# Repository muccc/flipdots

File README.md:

**Moved to https://git.muc.ccc.de/muccc/flipdots**

Software for some flipdot pannels we have.

http://wiki.muc.ccc.de/flipdot:start

ethersex-flipdot is a submodule which contains
firmware to receive and display data via ethernet.

netfbd is a submodule which contains a daemon
to grab parts of a linux framebuffer and send
via ethernet to the flipdots.

To init these submodules run 'git submodule init'
and 'git submodule update'.

When updating the repository, make sure to also run
'git submodule init' again, to get the lastest
changes inside the submodules.

scripts/ contains support scripts to send raw
test data to the flipdots.

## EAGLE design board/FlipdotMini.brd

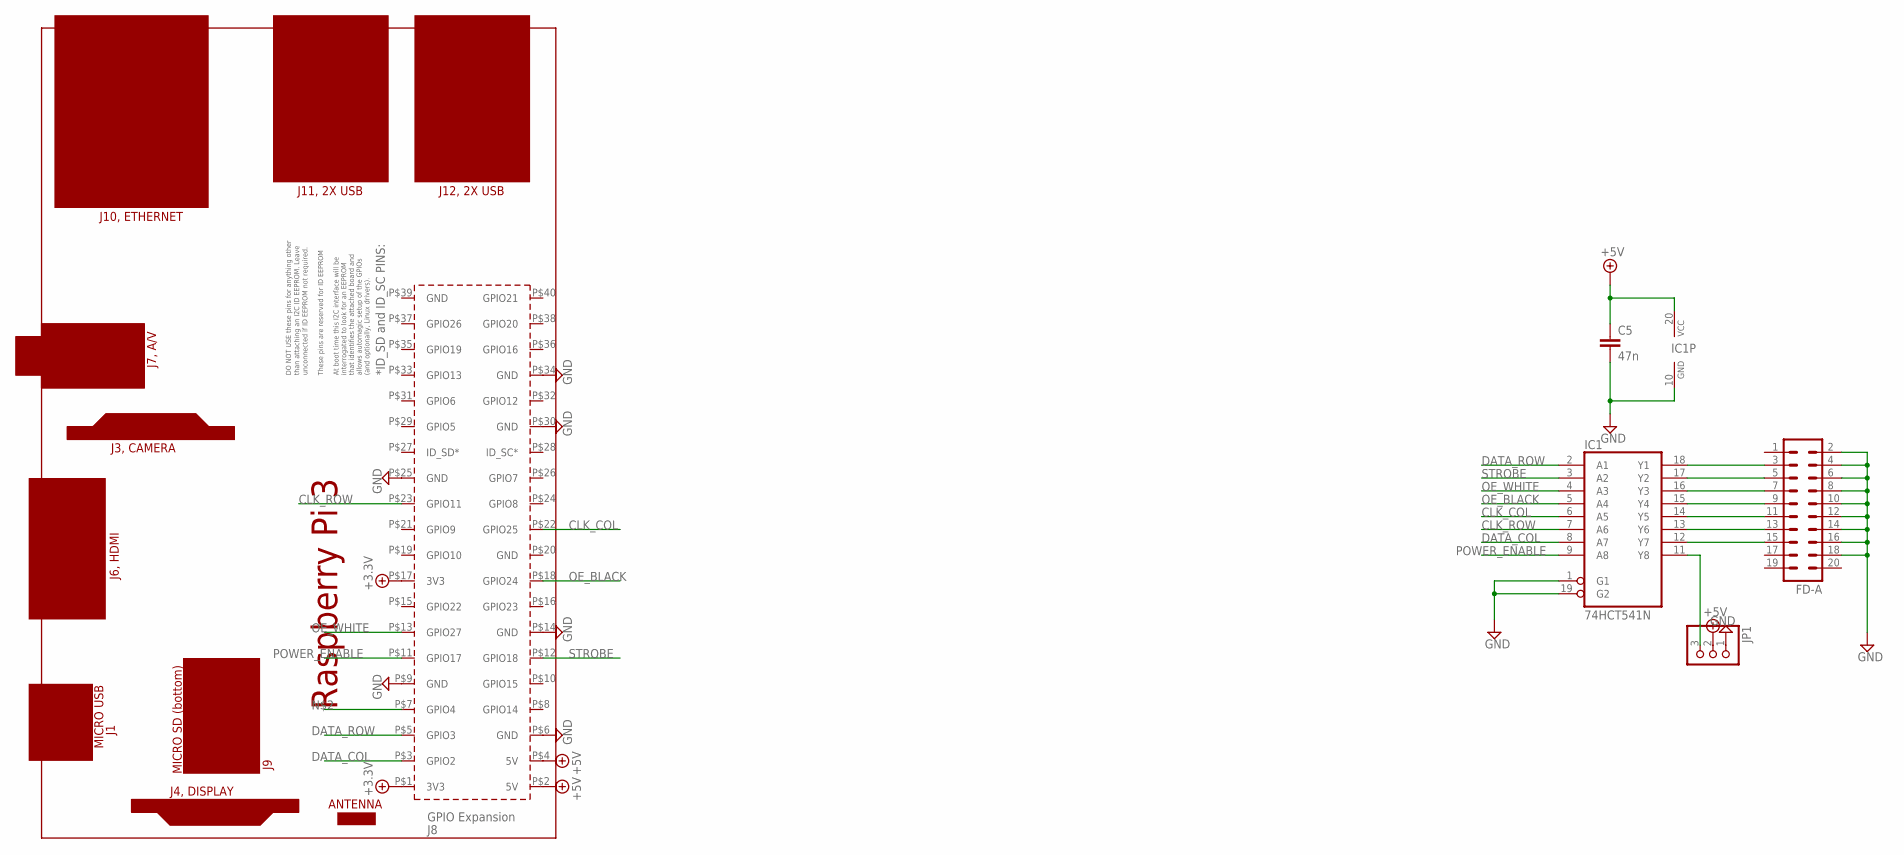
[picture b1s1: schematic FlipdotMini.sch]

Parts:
C5: 47n; C0805
FD-A: MA10-2
IC1: 74HCT541N; DIL20
JP1: PINHD-1X3; 1X03
PCB1: RPI3

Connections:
+3.3V: PCB1.P$1 (3V3), PCB1.P$17 (3V3)
+5V: C5.1, IC1.20 (VCC), JP1.2, PCB1.P$2 (5V), PCB1.P$4 (5V)
CLK_COL: IC1.6 (A5), PCB1.P$22 (GPIO25)
CLK_ROW: IC1.7 (A6), PCB1.P$23 (GPIO11)
DATA_COL: IC1.8 (A7), PCB1.P$3 (GPIO2)
DATA_ROW: IC1.2 (A1), PCB1.P$5 (GPIO3)
GND: C5.2, FD-A.2, FD-A.4, FD-A.6, FD-A.8, FD-A.10, FD-A.12, FD-A.14, FD-A.16, FD-A.18, IC1.1 (G1), IC1.10 (GND), IC1.19 (G2), JP1.1, PCB1.P$6 (GND), PCB1.P$9 (GND), PCB1.P$14 (GND), PCB1.P$25 (GND), PCB1.P$30 (GND), PCB1.P$34 (GND)
unnamed: FD-A.3, IC1.18 (Y1)
unnamed: FD-A.5, IC1.17 (Y2)
unnamed: FD-A.7, IC1.16 (Y3)
unnamed: FD-A.9, IC1.15 (Y4)
unnamed: FD-A.11, IC1.14 (Y5)
unnamed: FD-A.13, IC1.13 (Y6)
unnamed: FD-A.15, IC1.12 (Y7)
unnamed: IC1.11 (Y8), JP1.3
OE_BLACK: IC1.5 (A4), PCB1.P$18 (GPIO24)
OE_WHITE: IC1.4 (A3), PCB1.P$13 (GPIO27)
POWER_ENABLE: IC1.9 (A8), PCB1.P$11 (GPIO17)
STROBE: IC1.3 (A2), PCB1.P$12 (GPIO18)

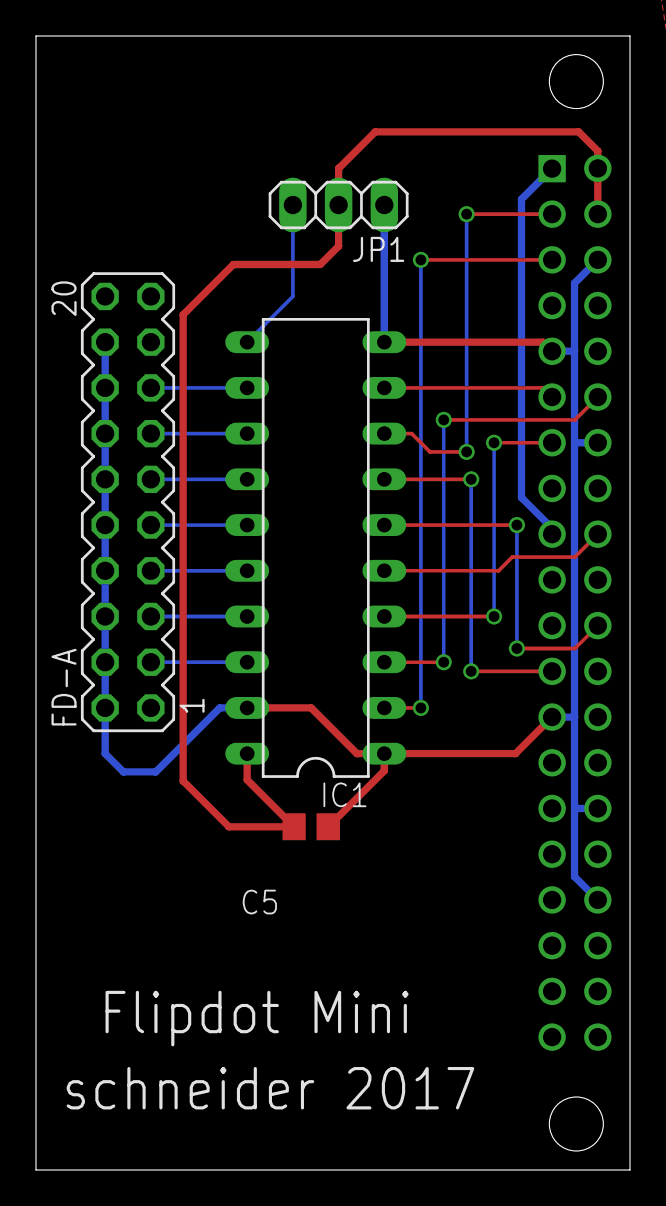
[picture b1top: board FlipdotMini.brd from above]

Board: 2 copper layers, 33.0 x 63.0 mm, 5 parts (0 on the bottom side), 19 nets.

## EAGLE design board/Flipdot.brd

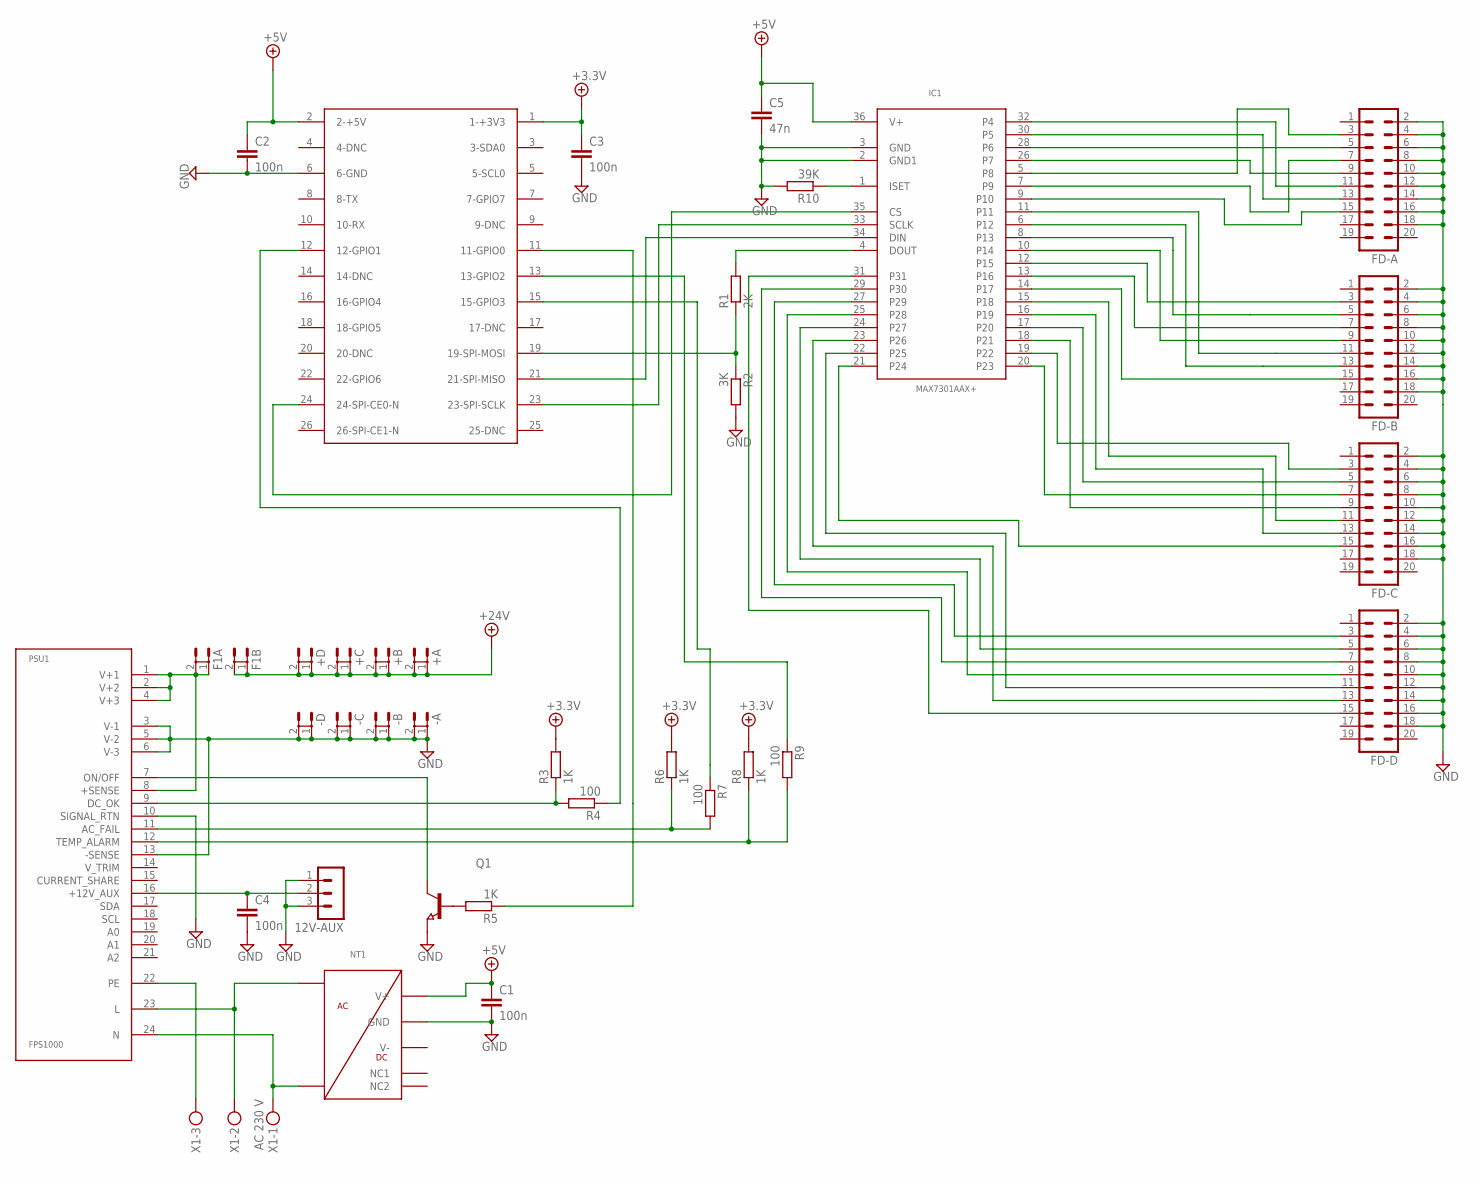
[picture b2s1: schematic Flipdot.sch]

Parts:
12V-AUX: MA03-1
+A: ST6,3
+B: ST6,3
+C: ST6,3
+D: ST6,3
-A: ST6,3
-B: ST6,3
-C: ST6,3
-D: ST6,3
C1, C2, C3, C4: 100n; C0603
C5: 47n; C0603
F1A, F1B: ST6,3
FD-A: MA10-2
FD-B: MA10-2
FD-C: MA10-2
FD-D: MA10-2
IC1: MAX7301AAX+; SSOP36
NT1: TMPM04; TPM04
PSU1: FPS1000; 24W9F
Q1: NPN-TRANSISTOR_SOT23; SOT23
R1: 2K; R0603
R2: 3K; R0603
R3, R5, R6, R8: 1K; R0603
R4, R7, R9: 100; R0603
R10: 39K; R0603
U$1: RASPBERRY-PI
X1: AC 230 V; MKDSN1,5/3-5,08

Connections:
+3.3V: C3.1, R3.2, R6.2, R8.2, U$1.1 (1-+3V3)
+5V: C1.1, C2.1, C5.1, IC1.36 (V+), NT1.3 (V+), U$1.2 (2-+5V)
+24V: +A.1, +A.2, +B.1, +B.2, +C.1, +C.2, +D.1, +D.2, F1B.1, F1B.2
GND: 12V-AUX.1, 12V-AUX.3, -A.1, -A.2, -B.1, -B.2, -C.1, -C.2, -D.1, -D.2, C1.2, C2.2, C3.2, C4.2, C5.2, FD-A.2, FD-A.4, FD-A.6, FD-A.8, FD-A.10, FD-A.12, FD-A.14, FD-A.16, FD-A.18, FD-B.2, FD-B.4, FD-B.6, FD-B.8, FD-B.10, FD-B.12, FD-B.14, FD-B.16, FD-B.18, FD-C.2, FD-C.4, FD-C.6, FD-C.8, FD-C.10, FD-C.12, FD-C.14, FD-C.16, FD-C.18, FD-D.2, FD-D.4, FD-D.6, FD-D.8, FD-D.10, FD-D.12, FD-D.14, FD-D.16, FD-D.18, IC1.2 (GND1), IC1.3 (GND), NT1.4 (GND), PSU1.3 (V-1), PSU1.5 (V-2), PSU1.6 (V-3), PSU1.10 (SIGNAL_RTN), PSU1.13 (-SENSE), Q1.2 (E), R2.2, R10.2, U$1.6 (6-GND)
unnamed: FD-D.11, IC1.22 (P25)
unnamed: FD-D.13, IC1.23 (P26)
unnamed: FD-A.5, IC1.28 (P6)
unnamed: FD-A.9, IC1.26 (P7)
unnamed: FD-A.3, IC1.5 (P8)
unnamed: FD-A.7, IC1.7 (P9)
unnamed: FD-A.15, IC1.9 (P10)
unnamed: FD-B.5, IC1.8 (P13)
unnamed: FD-B.9, IC1.10 (P14)
unnamed: FD-B.3, IC1.12 (P15)
unnamed: FD-B.7, IC1.13 (P16)
unnamed: FD-B.15, IC1.14 (P17)
unnamed: FD-C.5, IC1.17 (P20)
unnamed: FD-C.9, IC1.18 (P21)
unnamed: FD-C.3, IC1.19 (P22)
unnamed: FD-C.7, IC1.20 (P23)
unnamed: FD-C.15, IC1.21 (P24)
unnamed: FD-D.5, IC1.24 (P27)
unnamed: FD-D.9, IC1.25 (P28)
unnamed: FD-D.3, IC1.27 (P29)
unnamed: FD-D.7, IC1.29 (P30)
unnamed: FD-D.15, IC1.31
unnamed: IC1.33 (SCLK), U$1.23 (23-SPI-SCLK)
unnamed: IC1.35 (CS), U$1.24 (24-SPI-CE0-N)
unnamed: IC1.34 (DIN), U$1.21 (21-SPI-MISO)
unnamed: F1A.1, F1A.2, PSU1.1 (V+1), PSU1.2 (V+2), PSU1.4 (V+3), PSU1.8 (+SENSE)
unnamed: Q1.1 (B), R5.2
unnamed: PSU1.7 (ON/OFF), Q1.3 (C)
unnamed: PSU1.9 (DC_OK), R3.1, R4.2
unnamed: R5.1, U$1.11 (11-GPIO0)
unnamed: R4.1, U$1.12 (12-GPIO1)
unnamed: PSU1.11 (AC_FAIL), R6.1, R7.2
unnamed: R9.1, U$1.13 (13-GPIO2)
unnamed: PSU1.12 (TEMP_ALARM), R8.1, R9.2
unnamed: R7.1, U$1.15 (15-GPIO3)
unnamed: PSU1.22 (PE), X1.3
unnamed: FD-B.13, IC1.6 (P12)
unnamed: IC1.4 (DOUT), R1.2
unnamed: R1.1, R2.1, U$1.19 (19-SPI-MOSI)
unnamed: FD-B.11, IC1.11
unnamed: FD-C.11, IC1.15 (P18)
unnamed: FD-A.11, IC1.32 (P4)
unnamed: FD-C.13, IC1.16 (P19)
unnamed: FD-A.13, IC1.30 (P5)
unnamed: NT1.6 (N), PSU1.24 (N), X1.1
unnamed: NT1.7 (L), PSU1.23 (L), X1.2
unnamed: IC1.1 (ISET), R10.1
unnamed: 12V-AUX.2, C4.1, PSU1.16 (+12V_AUX)
NC1: NT1.1 (NC1)
NC2: NT1.2 (NC2)
V-: NT1.5 (V-)

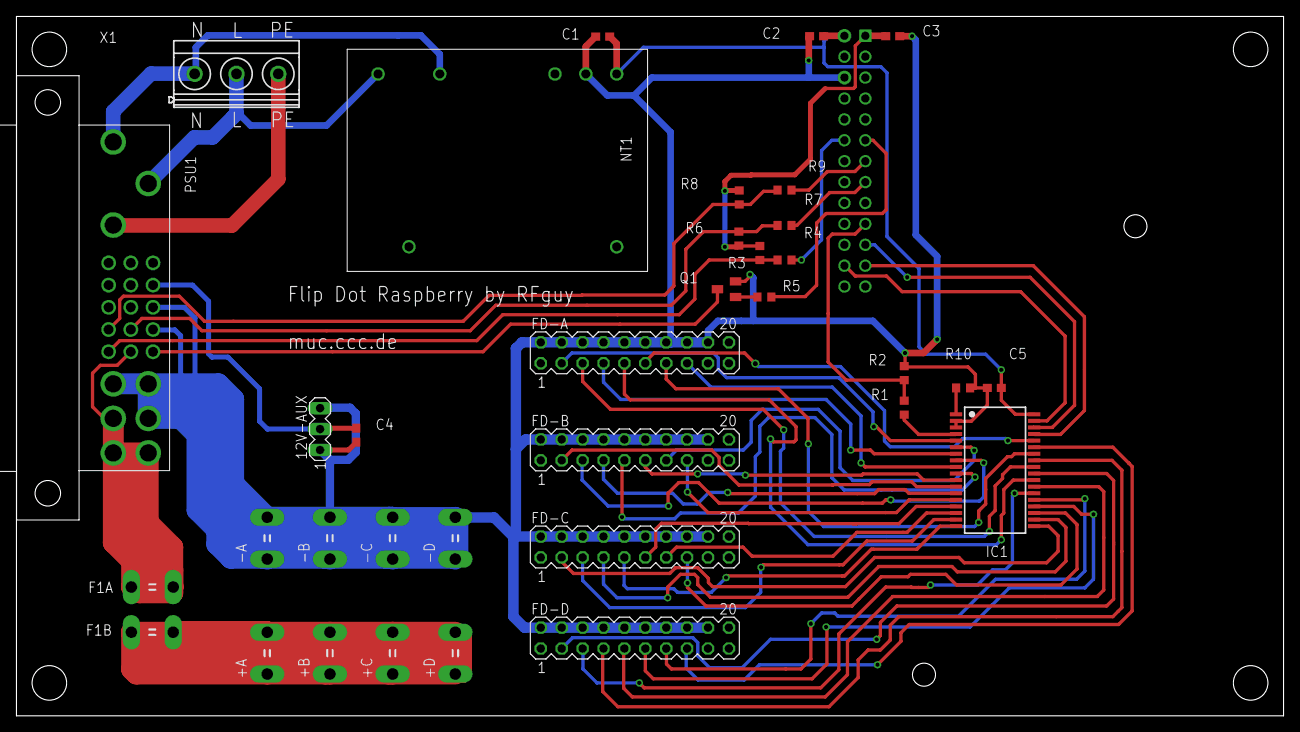
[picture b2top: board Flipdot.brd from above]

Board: 2 copper layers, 154.0 x 85.0 mm, 36 parts (1 on the bottom side), 52 nets.

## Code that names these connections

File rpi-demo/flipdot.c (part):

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#define SETBIT(x,i) x[i>>3]|=(1<<(i&7));

#define DATA(reg)                                \
    ((reg == ROW) ? pinning.data_row : pinning.data_col)
#define CLK(reg)                                \
    ((reg == ROW) ? pinning.clk_row : pinning.clk_col)

static uint8_t buffer_a[DISP_BYTE_COUNT];
static uint8_t buffer_b[DISP_BYTE_COUNT];
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
static void display_frame_differential(uint8_t *to_0, uint8_t *to_1);

#define PIN_POWER_ENABLE    RPI_V2_GPIO_P1_11
// XXX: Change to symbolic defines like RPI_V2_GPIO_P1_03
flipdot_pinning pinning =
{
    .data_col = RPI_V2_GPIO_P1_03, .data_row = RPI_V2_GPIO_P1_05, .strobe = RPI_V2_GPIO_P1_12, .oe_white = RPI_V2_GPIO_P1_13, .oe_black = RPI_V2_GPIO_P1_18, .clk_col = RPI_V2_GPIO_P1_22, .clk_row = RPI_V2_GPIO_P1_23
};

static uint8_t flipper[256];
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        return 1;

    /* init pins */
    bcm2835_gpio_fsel(PIN_POWER_ENABLE, BCM2835_GPIO_FSEL_OUTP);

    bcm2835_gpio_fsel(pinning.data_col, BCM2835_GPIO_FSEL_OUTP);
    bcm2835_gpio_fsel(pinning.data_row, BCM2835_GPIO_FSEL_OUTP);
    bcm2835_gpio_fsel(pinning.strobe, BCM2835_GPIO_FSEL_OUTP);
    bcm2835_gpio_fsel(pinning.oe_white, BCM2835_GPIO_FSEL_OUTP);
    bcm2835_gpio_fsel(pinning.oe_black, BCM2835_GPIO_FSEL_OUTP);
    bcm2835_gpio_fsel(pinning.clk_col, BCM2835_GPIO_FSEL_OUTP);
    bcm2835_gpio_fsel(pinning.clk_row, BCM2835_GPIO_FSEL_OUTP);

    /* Init buffer pointers */
    buffer_new = buffer_a;
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void
flipdot_power_on(void)
{
    bcm2835_gpio_write(PIN_POWER_ENABLE, OH);
    while(bcm2835_gpio_lev(PIN_POWER_ENABLE) == OL){
        printf("Power set error\n");
        bcm2835_gpio_write(PIN_POWER_ENABLE, OH);
    }
}

void
flipdot_power_off(void)
{
    bcm2835_gpio_write(PIN_POWER_ENABLE, OL);
    while(bcm2835_gpio_lev(PIN_POWER_ENABLE) == OH){
        printf("Power clear error\n");
        bcm2835_gpio_write(PIN_POWER_ENABLE, OL);
    }
}

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static void
strobe(void)
{
    bcm2835_gpio_write(pinning.strobe, OH);
    while(bcm2835_gpio_lev(pinning.strobe) == OL){
        printf("Strobe set error\n");
        bcm2835_gpio_write(pinning.strobe, OH);
    }
    _delay_us(STROBE_DELAY);
    bcm2835_gpio_write(pinning.strobe, OL);
    while(bcm2835_gpio_lev(pinning.strobe) == OH){
        printf("Strobe clear error\n");
        bcm2835_gpio_write(pinning.strobe, OL);
    }
}

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flip_white_start(void)
{
    timer_start();
    bcm2835_gpio_write(pinning.oe_black, OL);
    while(bcm2835_gpio_lev(pinning.oe_black) == OH){
        printf("OE black clear error\n");
        bcm2835_gpio_write(pinning.oe_black, OL);
    }
    bcm2835_gpio_write(pinning.oe_white, OH);
    while(bcm2835_gpio_lev(pinning.oe_white) == OL){
        printf("OE white set error\n");
        bcm2835_gpio_write(pinning.oe_white, OH);
    }
}

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flip_white_stop(void)
{
    timer_wait(FLIP_DELAY_WHITE);
    bcm2835_gpio_write(pinning.oe_black, OL);
    while(bcm2835_gpio_lev(pinning.oe_black) == OH){
        printf("OE black clear error\n");
        bcm2835_gpio_write(pinning.oe_black, OL);
    }
    bcm2835_gpio_write(pinning.oe_white, OL);
    while(bcm2835_gpio_lev(pinning.oe_white) == OH){
        printf("OE white clear error\n");
        bcm2835_gpio_write(pinning.oe_white, OL);
    }
}

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flip_black_start(void)
{
    timer_start();
    bcm2835_gpio_write(pinning.oe_black, OH);
    while(bcm2835_gpio_lev(pinning.oe_black) == OL){
        printf("OE black set error\n");
        bcm2835_gpio_write(pinning.oe_black, OH);
    }
    bcm2835_gpio_write(pinning.oe_white, OL);
    while(bcm2835_gpio_lev(pinning.oe_white) == OH){
        printf("OE white clear error\n");
        bcm2835_gpio_write(pinning.oe_white, OL);
    }
}

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flip_black_stop(void)
{
    timer_wait(FLIP_DELAY_BLACK);
    bcm2835_gpio_write(pinning.oe_black, OL);
    while(bcm2835_gpio_lev(pinning.oe_black) == OH){
        printf("OE black clear error\n");
        bcm2835_gpio_write(pinning.oe_black, OL);
    }
    bcm2835_gpio_write(pinning.oe_white, OL);
    while(bcm2835_gpio_lev(pinning.oe_white) == OH){
        printf("OE white clear error\n");
        bcm2835_gpio_write(pinning.oe_white, OL);
    }
}

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
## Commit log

2013-02-05 Added .gitignore draft
2013-02-07 Added Makefile
2013-02-07 Added curren main.c
2013-06-15 Stuff is working
2013-06-15 Threw out old code and wrote some functions that abstract shift register filling.
2013-06-15 add link to wiki
2013-06-15 Display now works but bits inside bytes are displayed in wrong order. Beware messy code!
2013-06-16 Added #includes that include xbm files which will be played back at high framerate
2013-06-16 added test script to send something to two panels
2013-06-16 wrong file...
2013-06-16 Added two new demos
2013-06-17 Removed Bit-Reversing; no more necessary after change in flipdot-ethersex by s
2013-06-17 Space invaders invading your flipdots
2013-06-17 alarm
2013-06-17 removed old files
2013-06-17 moved testsender to scripts directory
2013-06-17 added the ethersex-flipdot and netfbd repos as submodules
2013-06-17 moved some scripts
2013-06-17 little helper script to generate imagemaps
2013-06-23 working differential version of ethersex-flipdot
2013-06-23 Added zero boundary conditions, restart on no change and correct resolution for golflip Changed mac addresses
2013-06-23 Updated to new embedded flipdot driver with differential display
2013-06-23 Added a noise.py script that shows white noise with a sine modulated power
2013-06-23 Gen string can send what it gets on stdin
2013-06-23 Blah
2013-06-23 gen_string.py: use utf-8 encoding
2013-06-23 typo: s/DAILY/DELAY/
2013-06-23 update ethersex-flipdot submodule
2013-06-23 updated readme for submodule
2013-06-29 simple python snake game
2013-06-29 cleanups
2013-06-29 wrong ident
2013-06-29 new setting WRAP_BORDERS
2013-06-29 Added simple mqtt highscore support using test.mosquitto.org.
2013-06-29 Added sine
2013-06-29 Food blinks
2013-06-29 No mosquitto needed anymore. If highscore is wanted please install mosquitto for python (using pip for example)
2013-06-30 added an example level
2013-06-30 added some code to load levels
2013-06-30 use terminal colors for curses instead of a black bg
2013-06-30 added some more documentation
2013-06-30 don't place food into walls
2013-06-30 bugfix agains walls...
2013-06-30 added level to test anti-wall-placement and fixed it
2013-06-30 added another level
2013-06-30 slower blink frequency for the food
2013-06-30 added settings file
2013-06-30 added classic level
2013-06-30 p for pause
2013-06-30 Some bugs fixed
2013-06-30 Fixed unnecessary bug.
2013-07-01 moved old scripts to archive
2013-07-01 added .pyc and project-files to gitignore
2013-07-01 New python api with hq status script
2013-07-01 fixed a small bug in hqstatus
2013-07-01 gen_string
2013-07-02 LineBreak
2013-09-16 Adding Board
2013-09-22 feat(simplespi): add libsimplespi
2013-09-22 feat(max7301): add libmax7301
2013-09-22 fix(makefiles): remove binaries of libraries
2013-09-22 fix(max7301): fix nasty off by one
2013-09-22 doc(max7301): add the README file
2013-09-24 fix(libmax7301): copy the header to /usr/local/include
2013-09-24 feat(rpi-demo): add demo for rpi
2013-09-24 feat(rpi-demo): add scripts to control the 24 V supply
2013-09-25 control 3 panels
2013-09-26 feat(rpi-demo): small performance improvement
2013-09-26 fix(rpi-demo): use correct module count and account for row gap
2013-09-26 fix(rpi-demo): fix output of power_on script
2013-09-26 feat(rpi-demo): different delays for b&w, bit order inversion
2013-09-26 feat(rpi-demo): flipdot udp receiver
2013-09-27 fix(board): move gpio from pin 17 to pin 3
2013-09-29 fix(rpidemo): move to IPv6
2013-10-02 gameoflife for flipdot \o/
2013-10-22 added scripts to convert and send image data
2013-10-22 ipv6 and all addresses
2013-10-27 fix(udp-receiver): do not clear the displya right after booting
2013-11-04 support for all 3 assemblies
2013-11-04 add large huge seedfile example
2013-11-16 Added transposed matrix
2013-11-16 BETA: MultiMatrixAPI
2013-11-23 add flipdot poster
2013-11-23 replace uns->CCC München
2013-11-24 Fix QR code, added readme about pixel font
2013-11-29 convert poster to a2 landscape
2013-11-29 Remove delimiter
2014-01-01 added game written at 30c3.
    This version is a cleaned up version of the game running at 30c3.
    Since I don't have any hardware to test it, I have no idea if it
    works. I think it should. :)
2014-03-12 feat(udp-receiver): made the display size configurable
2014-03-12 doc(udp-receiver): readme
2014-03-18 stuff to measure performance i think
2014-03-18 i don't known anymore...
2014-04-20 feat(SoMakeIt): Added documentation for the SoMakeIt panel and the modified script
2014-12-27 API with 31c3 IPs
2014-12-27 antifnord
2014-12-27 BETA: pad2flipdotscript
2014-12-27 on change
2014-12-27 debug: only on change
2014-12-27 maximal 2000 zeichen
2014-12-27 static url
2014-12-29 initial opencv test, order/orientation of the displays still flawed
2014-12-29 corrected display settings
2014-12-29 added threshold image example
2014-12-29 added README
2014-12-29 rm debug output
2014-12-29 simple xkcd grabber added
2014-12-29 scroll_image test
2015-11-01 Fix display scrip for general use
2016-12-27 Added "throw etherpad to flipdotwall-script"
2017-02-18 UDP Receiver for the Zeile. Does magic translation things because of the orientation of the panels
2017-02-18 udp_receiver_and_translator: Add parameters and debug
2017-02-19 scripts: add clock
2017-02-19 clock: circulate in the right direction
2017-02-19 clock: implement command line parameters
2017-02-19 clock: transpone matrix to be suitable for FlipdotAPI
2017-02-19 made a simple debugApp
2017-02-19 clock: Add update interval parameter
2017-02-19 set to localhost and listen to v6
2017-02-19 ministyle
2017-02-19 parameter setup
2017-02-22 hoffentlich weniger "geisterbilder"
2017-03-01 change(flipdot): Fill registers while flipping
2017-03-02 fix(smileyflip): removed broken script
2017-03-02 feat(board): outline for a touch protection for the live parts.
2017-03-03 flipdotApi: no recursion in blitTextAtPosition
2017-03-03 FlipdotApi: Remove whitespaces
2017-03-03 FlipdotApi: store current ip/port config in separate file
2017-03-03 FlipdotAPI: remove all the API
2017-03-03 FlipdotAPI: add all the API as submodule
2017-03-03 Revert "FlipdotAPI: add all the API as submodule"
    This reverts commit eb84478022d6b79c39bd02108a55c11355e22dde.
2017-03-03 Revert "FlipdotAPI: remove all the API"
    This reverts commit 7363baba0cc0df4a09a433785ecb0e3e60f1599f.
2017-03-03 webapp: move to subdirectory
2017-03-03 webapp: spaces
2017-03-03 webapp: add example png mode
2017-03-03 webapp: commit missing import changes
2017-03-03 webapp: add flipdot-web-editor as submodule
2017-03-03 webapp: add link to web editor
2017-03-03 FlipdotAPI: switch to python3
2017-03-03 clock: python3
2017-03-03 FlipdotAPI: module fnord
2017-03-03 new translation for new wandsteuerungsanlage
2017-03-04 qr generator
2017-03-05 default config for the wand
2017-03-06 race: wip
2017-03-06 change(rpi-demo): Use direct port io via libbcm2835
2017-03-06 fix(rpi-demo): Current timings and pins
2017-03-06 chore(flipdot): Change tabs to spaces
2017-03-06 feat(udp-receiver): Catch CTRL+C
2017-03-06 chore(config): Update to new CLK_DELAY default
2017-03-06 fix(flipdot): Read GPIOs back to verify the change
2017-03-06 fixed buggy wand-mapping
2017-03-06 feat(flipdot): Print warnings when the GPIO write failed
2017-03-06 feat(udp-receiver): Pixel translator for flipdotwand
2017-03-06 feat(udp-receiver): Basic power control
2017-03-06 fix(flipdotapi): Remove typo in default address
2017-03-06 fix(webapp): Use default configuration from flipdotapi
2017-03-09 fix(clock): Only send an image if there was a change
2017-05-01 scripts: Add rudimentary pong game
2017-05-01 pong: try to center text
2017-05-01 pong: calculate sleep time
2017-05-03 pong: tremendous speed increase, noone has better speed increases
2017-05-03 FlipdotAPI: Start using numpy
2017-05-03 FlipdotAPI: use more numpy
2017-05-03 pong: flip fix
2017-05-03 flipdotAPI: add showImage
2017-05-03 pong: don't update flipdot when inactive
2017-05-03 pong: add command line option for scores file
2017-05-03 pong: Print warning when fps are too high for the system
2017-08-16 clock: implement smart-sleep
2017-08-16 FlipdotAPI: implement equal comparison for FlipdotImage
2017-08-16 clock: compare better
2017-08-16 tron: use python3 and adjust to current API
2017-08-16 webapp: add numpy to default.nix
2017-08-16 Add default.nix
2017-08-16 default.nix: Add NumPy
2017-08-16 Add template for flipdot application
2017-08-16 add clock.ipynb
2017-08-16 FlipdotMatrix: remove debug remains
2017-08-16 add clean function
2017-08-16 default.nix Add pygame
2017-08-16 pong_pygame_input: python3 and multiple simultaneous key presses
2017-08-17 add ipv4 support for input handler socket
2017-11-04 feat(board): FlipdotMini board
2018-06-04 feat(rpi-demo): Option to invert the outputs
2018-06-04 chore(rpi-demo): Clarify options for display_frame_differential
2018-06-05 chore(rpi-demo): Remove multiple bus support
2018-06-05 change(rpi-demo): INVERT -> INVERT_GPIO
2018-06-05 feat(rpi-demo): Option for mirrored cabling
2018-06-05 feat(rpi-demo): Simplify config
2018-07-08 feat(gif): Hacked together script to play gifs
2018-08-23 add script to get size of text in pixels
2018-08-23 feat(srt2gif): Simple text splitter
2018-08-23 add script to render scrolling lines
2018-08-23 take srt file as input
2018-08-23 fix sliding animation
2018-08-23 give more useful warning for text that's too close
2018-08-23 properly handle end of srt
2018-08-23 add quick usage notes
2018-08-23 actually fix end of animation
2019-02-19 fix(srt render): Use <10 FPS
2025-06-22 README: moved repo

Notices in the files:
rpi-demo/flipdot.c:
Copyright (c) 2013 Franz Nord
modify it under the terms of the GNU General Public License
For more information on the GPL, please go to:
http://www.gnu.org/copyleft/gpl.html
